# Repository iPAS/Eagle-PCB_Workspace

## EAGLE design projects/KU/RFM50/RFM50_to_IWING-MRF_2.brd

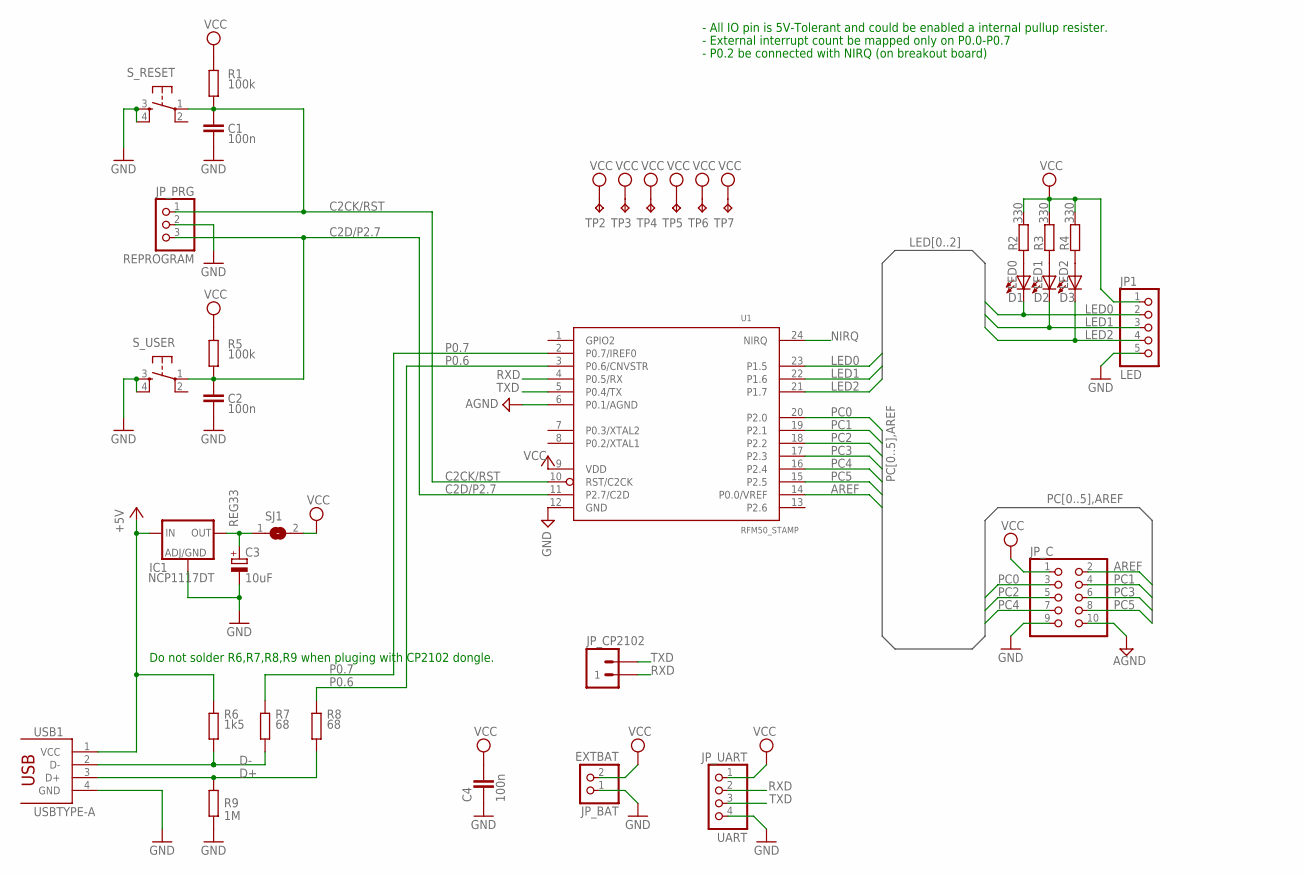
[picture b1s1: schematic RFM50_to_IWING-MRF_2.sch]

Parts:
C1, C2, C4: 100n; C050-024X044
C3: 10uF; E2,5-6E
D1: LED0; LED3MM
D2: LED1; LED3MM
D3: LED2; LED3MM
IC1: NCP1117DT; DPACK
JP1: LED; 1X05
JP_BAT: EXTBAT; 1X02
JP_C: HEADER-2X5; 2X05
JP_CP2102: M02PTH; 1X02
JP_PRG: REPROGRAM; 1X03
JP_UART: UART; 1X04_ROUND
R1, R5: 100k; 0204/5
R2, R3, R4: 330; 0204/5
R6: 1k5; 0204/5
R7, R8: 68; 0204/5
R9: 1M; 0204/5
SJ1: SOLDERJUMPERREFLOW_NOPASTE; SOLDERJUMPER_REFLOW_NOPASTE
S_RESET: DTS-6
S_USER: DTS-6
TP2, TP3, TP4, TP5, TP6, TP7: TPPAD1-10; P1-10_TP
U1: RFM50_STAMP
USB1: USBTYPE-A

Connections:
+5V: IC1.3 (IN), R6.1, USB1.1 (VCC)
AGND: JP_C.10, U1.6 (P0.1/AGND)
AREF: JP_C.2, U1.14 (P0.0/VREF)
C2CK/RST: C1.2, JP_PRG.1, R1.2, S_RESET.1, U1.10 (RST/C2CK)
C2D/P2.7: C2.2, JP_PRG.3, R5.2, S_USER.1, U1.11 (P2.7/C2D)
D+: R8.1, R9.2, USB1.3 (D+)
D-: R6.2, R7.1, USB1.2 (D-)
GND: C1.1, C2.1, C3.-, C4.1, IC1.1 (ADJ), JP1.5, JP_BAT.1, JP_C.9, JP_PRG.2, JP_UART.4, R9.1, S_RESET.3, S_RESET.4, S_USER.3, S_USER.4, U1.12 (GND), USB1.4 (GND)
LED0: D1.K (C), JP1.2, U1.23 (P1.5)
LED1: D2.K (C), JP1.3, U1.22 (P1.6)
LED2: D3.K (C), JP1.4, U1.21 (P1.7)
unnamed: D1.A, R2.2
unnamed: D2.A, R3.2
unnamed: D3.A, R4.2
NIRQ: U1.24 (NIRQ)
P0.6: R8.2, U1.3 (P0.6/CNVSTR)
P0.7: R7.2, U1.2 (P0.7/IREF0)
PC0: JP_C.3, U1.20 (P2.0)
PC1: JP_C.4, U1.19 (P2.1)
PC2: JP_C.5, U1.18 (P2.2)
PC3: JP_C.6, U1.17 (P2.3)
PC4: JP_C.7, U1.16 (P2.4)
PC5: JP_C.8, U1.15 (P2.5)
REG33: C3.+, IC1.4 (OUT), SJ1.1
RXD: JP_CP2102.1, JP_UART.2, U1.4 (P0.5/RX)
TXD: JP_CP2102.2, JP_UART.3, U1.5 (P0.4/TX)
VCC: C4.2, JP1.1, JP_BAT.2, JP_C.1, JP_UART.1, R1.1, R2.1, R3.1, R4.1, R5.1, SJ1.2, TP2.TP, TP3.TP, TP4.TP, TP5.TP, TP6.TP, TP7.TP, U1.9 (VDD)

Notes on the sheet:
- All IO pin is 5V-Tolerant and could be enabled a internal pullup resister.
- External interrupt count be mapped only on P0.0-P0.7
- P0.2 be connected with NIRQ (on breakout board)
Do not solder R6,R7,R8,R9 when pluging with CP2102 dongle.

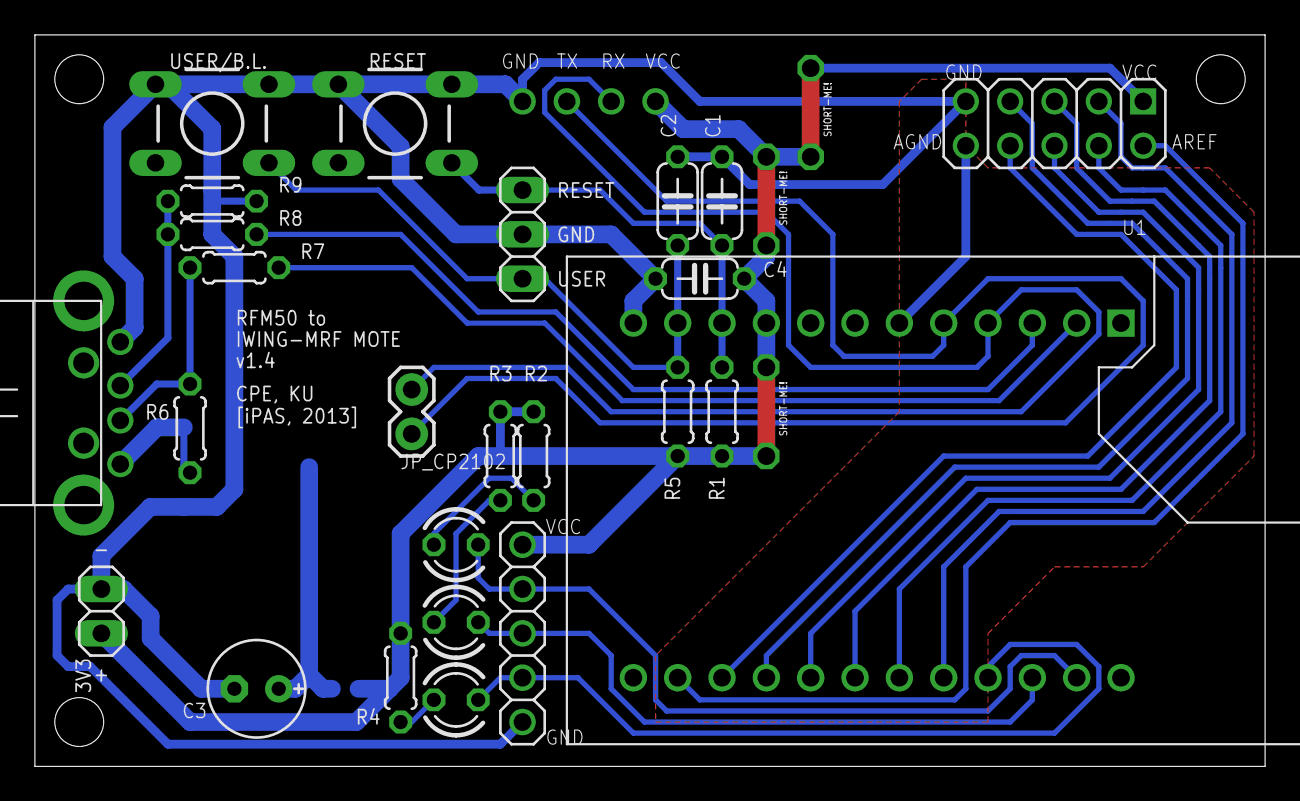
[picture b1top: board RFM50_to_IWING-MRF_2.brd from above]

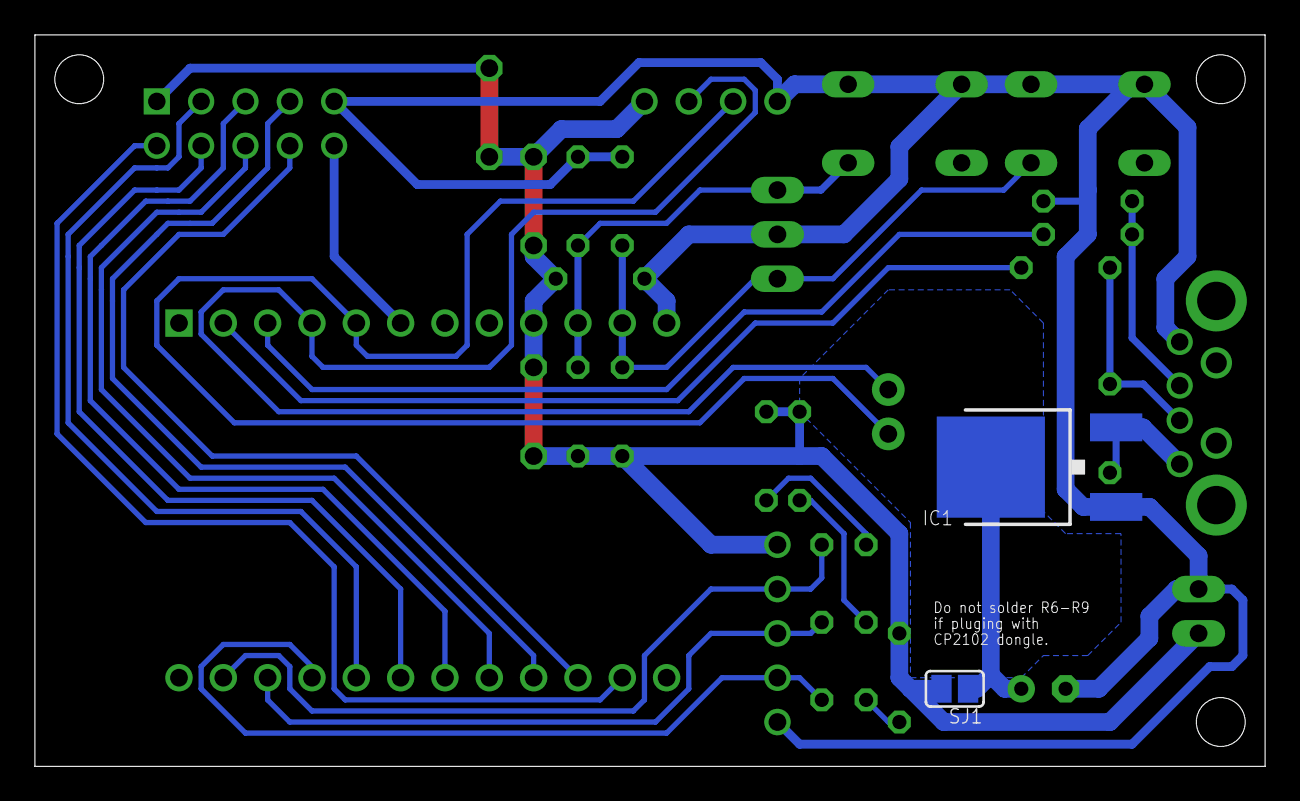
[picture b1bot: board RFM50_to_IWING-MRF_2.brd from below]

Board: 2 copper layers, 70.5 x 41.9 mm, 34 parts (2 on the bottom side), 26 nets.

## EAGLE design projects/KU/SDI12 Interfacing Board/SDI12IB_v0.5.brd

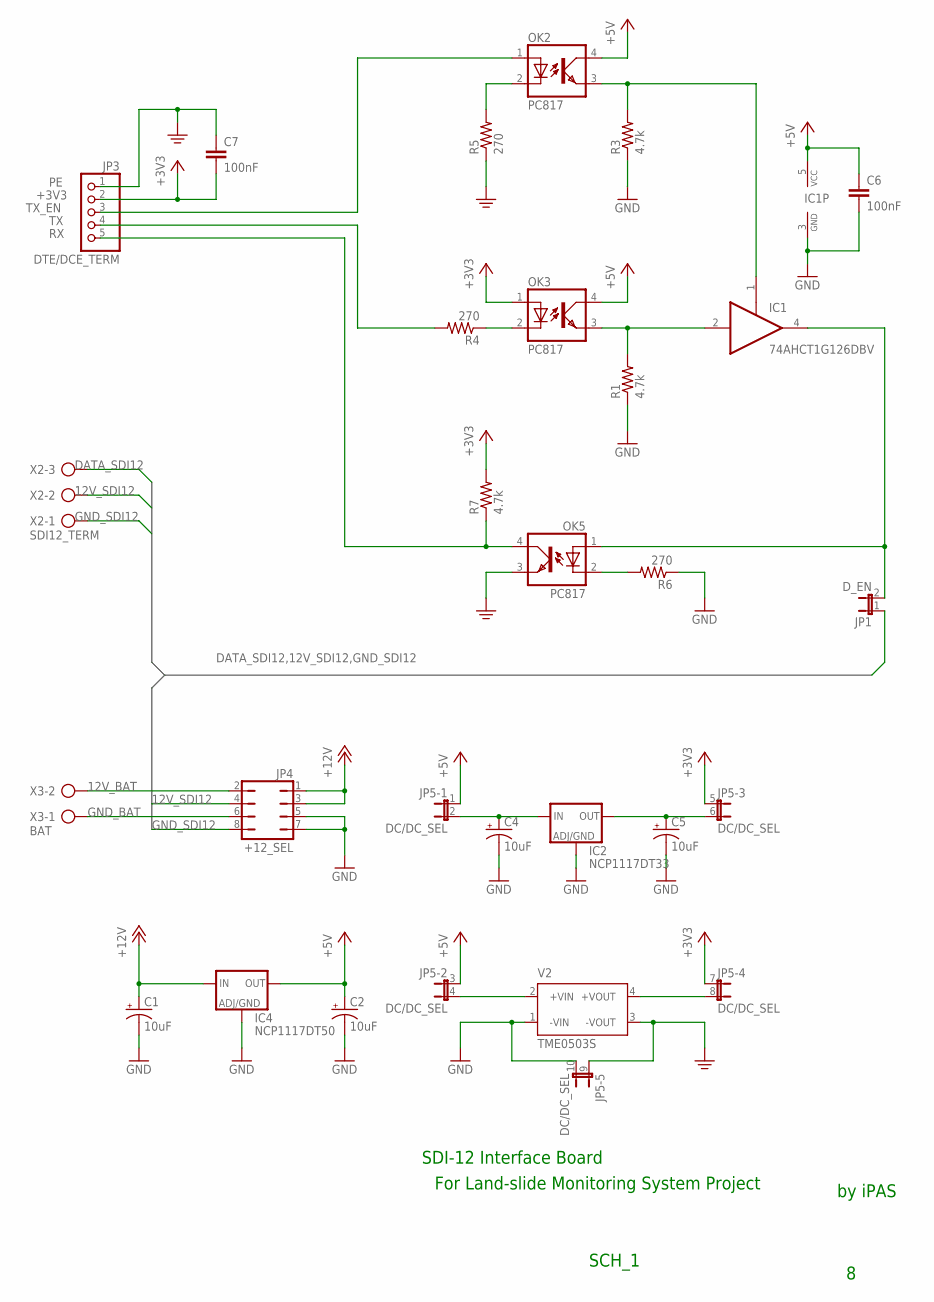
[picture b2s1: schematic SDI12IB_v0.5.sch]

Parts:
C1, C2, C4, C5: 10uF; E2-5
C6: 100nF; C1210
C7: 100nF; C050-025X075
IC1: 74AHCT1G126DBV; SOT23-5
IC2: NCP1117DT33; DPACK
IC4: NCP1117DT50; DPACK
JP1: D_EN; JP1
JP3: DTE/DCE_TERM; 1X05
JP4: +12_SEL; JP4Q
JP5: DC/DC_SEL; JP5Q
OK2, OK3, OK5: PC817; DIL04
R1, R3, R7: 4.7k; 0204/7
R4, R5, R6: 270; 0204/7
V2: TME0503S; TME
X2: SDI12_TERM; AK300/3
X3: BAT; AK300/2

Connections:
12V_BAT: JP4.2, X3.2
12V_SDI12: JP4.4, X2.2
+3V3: C7.2, JP3.2, JP5.5 (1), JP5.7 (1), OK3.1 (A), R7.2
+5V: C2.+, C6.1, IC1.5 (VCC), IC4.4 (OUT), JP5.1, JP5.3 (1), OK2.4 (COL), OK3.4 (COL)
+12V: C1.+, IC4.3 (IN), JP4.1, JP4.3
DATA_SDI12: JP1.1, X2.3
GND: C1.-, C2.-, C4.-, C5.-, C6.2, IC1.3 (GND), IC2.1 (ADJ), IC4.1 (ADJ), JP4.5, JP4.7, JP5.10 (2), R1.1, R3.1, R6.1, V2.1 (-VIN)
GND_BAT: JP4.6, X3.1
GND_SDI12: JP4.8, X2.1
unnamed: C4.+, IC2.3 (IN), JP5.2
unnamed: JP5.4 (2), V2.2 (+VIN)
unnamed: C5.+, IC2.4 (OUT), JP5.6 (2)
unnamed: IC1.2 (I), OK3.3 (EMIT), R1.2
unnamed: OK3.2 (C), R4.1
unnamed: JP5.8 (2), V2.4 (+VOUT)
unnamed: IC1.1 (OE), OK2.3 (EMIT), R3.2
unnamed: OK2.2 (C), R5.2
unnamed: OK5.2 (C), R6.2
unnamed: IC1.4 (O), JP1.2, OK5.1 (A)
PE: C7.1, JP3.1, JP5.9 (1), OK5.3 (EMIT), R5.1, V2.3 (-VOUT)
RX: JP3.5, OK5.4 (COL), R7.1
TX: JP3.4, R4.2
TX_EN: JP3.3, OK2.1 (A)

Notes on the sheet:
SDI-12 Interface Board
SCH_1
by iPAS
For Land-slide Monitoring System Project

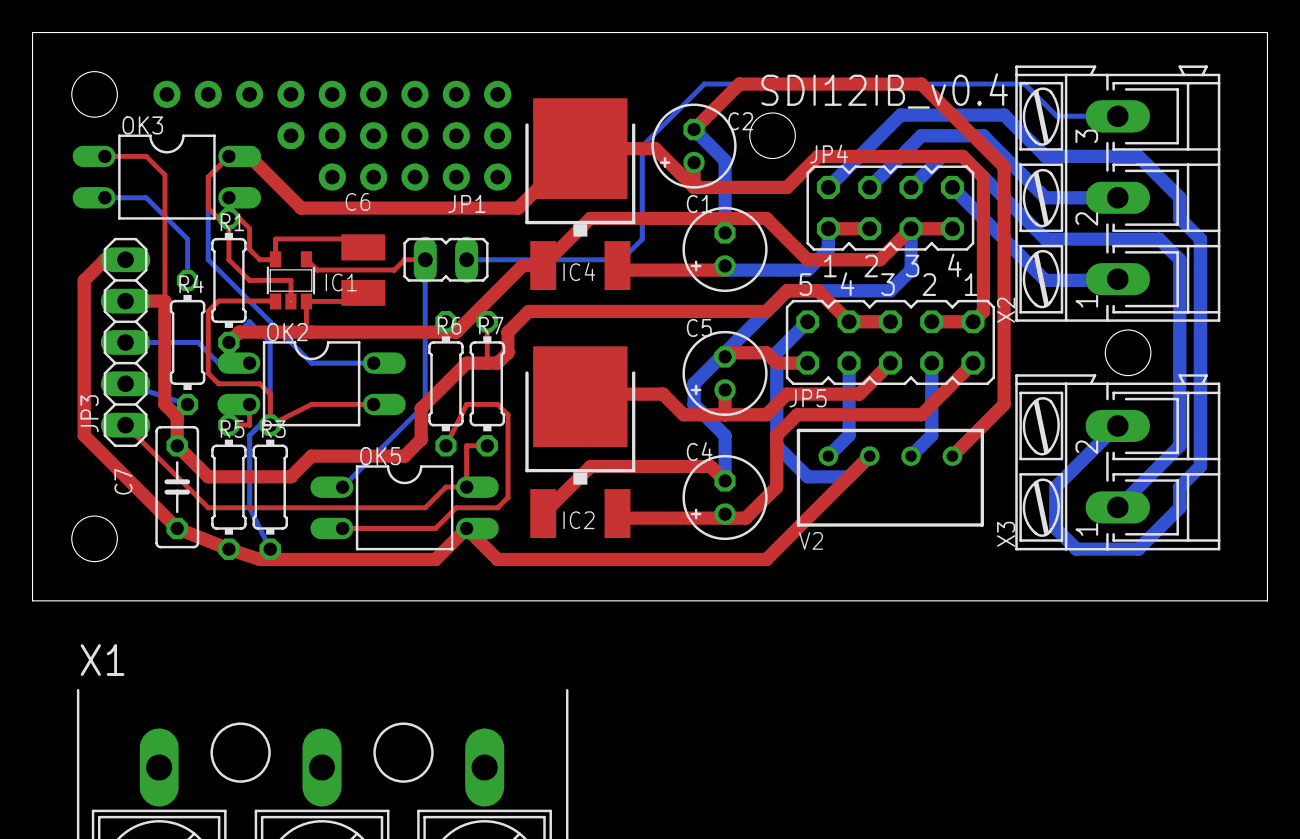
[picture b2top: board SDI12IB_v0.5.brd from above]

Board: 2 copper layers, 75.9 x 34.9 mm, 26 parts (0 on the bottom side), 23 nets.

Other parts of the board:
X1: W239-103

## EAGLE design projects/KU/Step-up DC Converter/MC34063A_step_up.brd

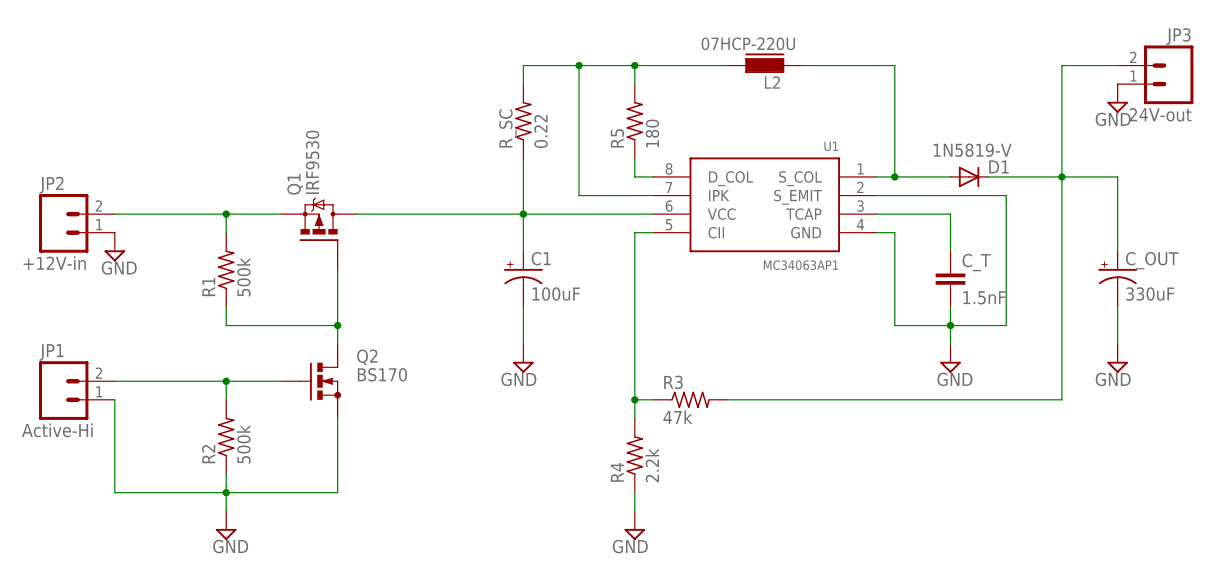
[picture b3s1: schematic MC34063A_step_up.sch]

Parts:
C1: 100uF; RCL_E5-10,5
C_OUT: 330uF; RCL_E5-10,5
C_T: 1.5nF; RCL_C025-024X044
D1: 1N5819-V; DO41-150V
JP1: Active-Hi; 1X02
JP2: +12V-in; 1X02
JP3: 24V-out; 1X02
L2: 07HCP-220U; FASTRON_07HCP_INDUCTOR
Q1: IRF9530; TO220BV
Q2: BS170; TO92-
R1, R2: 500k; RCL_0204V
R3: 47k; RCL_0204V
R4: 2.2k; RCL_0204V
R5: 180; RCL_0204V
R_SC: 0.22; RCL_0204V
U1: MC34063AP1; DIL08

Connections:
GND: C1.-, C_OUT.-, C_T.2, JP1.1, JP2.1, JP3.1, Q2.3 (S), R2.1, R4.1, U1.2 (S_EMIT), U1.4 (GND)
unnamed: D1.A, L2.1, U1.1 (S_COL)
unnamed: JP2.2, Q1.S, R1.2
unnamed: Q1.G, Q2.1 (D), R1.1
unnamed: JP1.2, Q2.2 (G), R2.2
unnamed: C_OUT.+, D1.C, JP3.2
unnamed: C_T.1, U1.3 (TCAP)
unnamed: R5.1, U1.8 (D_COL)
unnamed: L2.2, R5.2, R_SC.2, U1.7 (IPK)
unnamed: R3.1, R4.2, U1.5 (CII)
unnamed: C1.+, Q1.D, R_SC.1, U1.6 (VCC)

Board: 2 copper layers, 17 parts (0 on the bottom side), 11 nets, no tracks yet.

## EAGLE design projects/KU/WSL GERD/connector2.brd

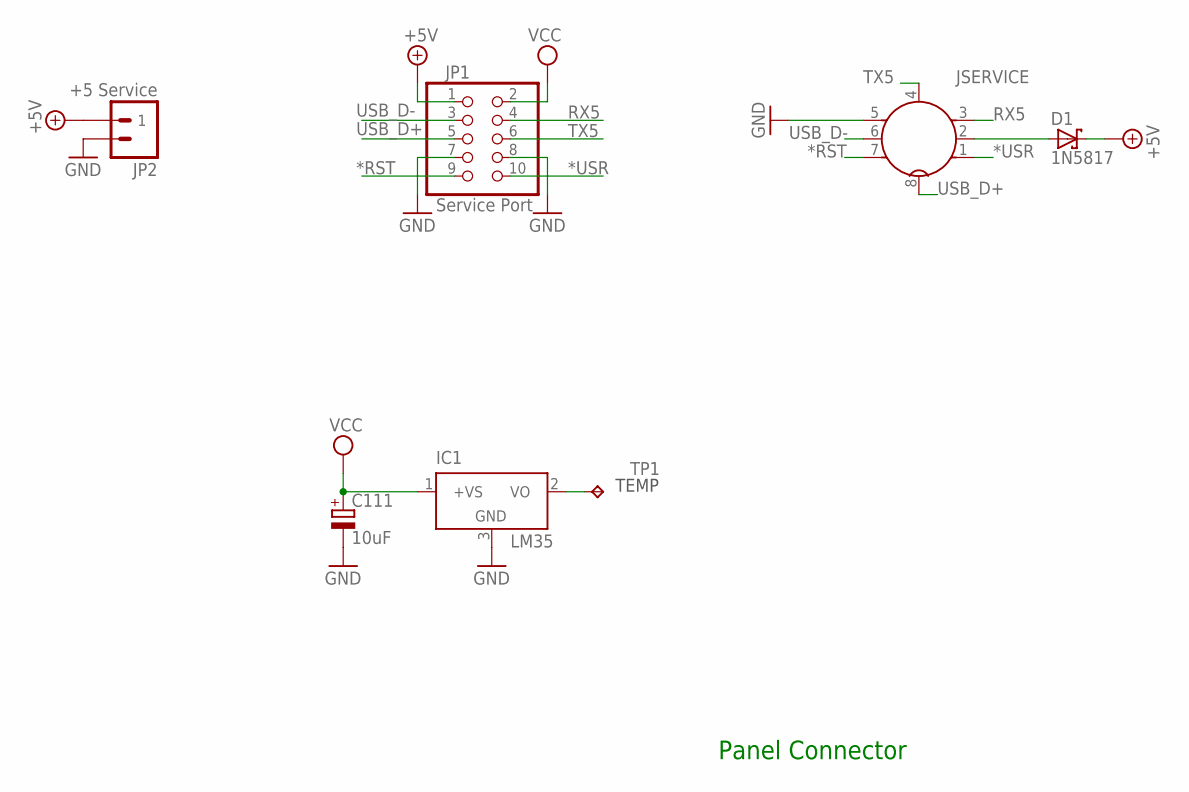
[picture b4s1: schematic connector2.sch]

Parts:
C111: 10uF; E2,5-6E
D1: 1N5817; DO41-150V
IC1: LM35; TO92-50
JP1: Service Port; 2X05
JP2: +5 Service; MOLEX-1X2
JSERVICE: MIC_CONN_MALE_8P
TP1: TPPAD1-13; P1-13

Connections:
*RST: JP1.9, JSERVICE.7
*USR: JP1.10, JSERVICE.1
+5V: D1.C, JP1.1, JP2.1
GND: C111.-, IC1.3 (GND), JP1.7, JP1.8, JP2.2, JSERVICE.5
unnamed: D1.A, JSERVICE.2
unnamed: IC1.2 (VO), TP1.TP
RX5: JP1.4, JSERVICE.3
TX5: JP1.6, JSERVICE.4
USB_D+: JP1.5, JSERVICE.8
USB_D-: JP1.3, JSERVICE.6
VCC: C111.+, IC1.1 (+VS), JP1.2

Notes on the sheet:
Panel Connector

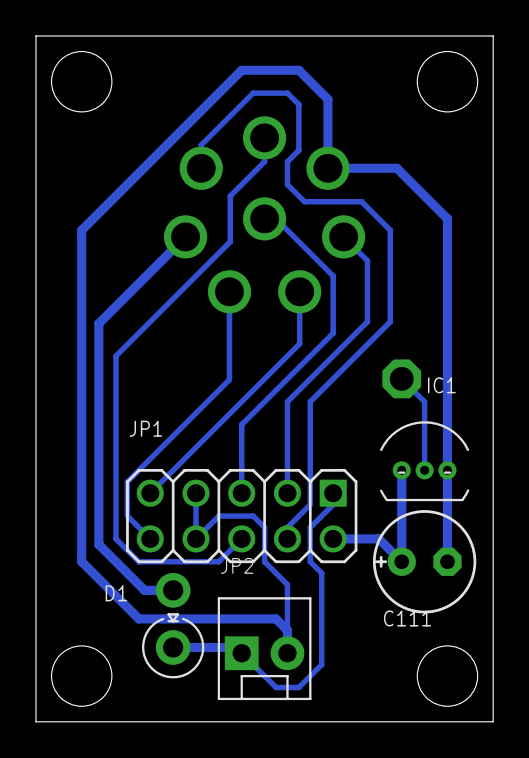
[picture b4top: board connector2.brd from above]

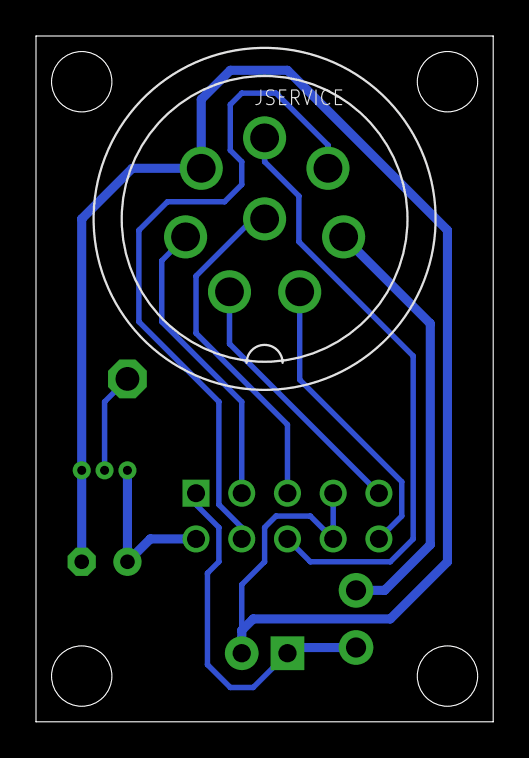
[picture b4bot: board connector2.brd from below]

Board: 2 copper layers, 25.4 x 38.1 mm, 7 parts (2 on the bottom side), 11 nets.
